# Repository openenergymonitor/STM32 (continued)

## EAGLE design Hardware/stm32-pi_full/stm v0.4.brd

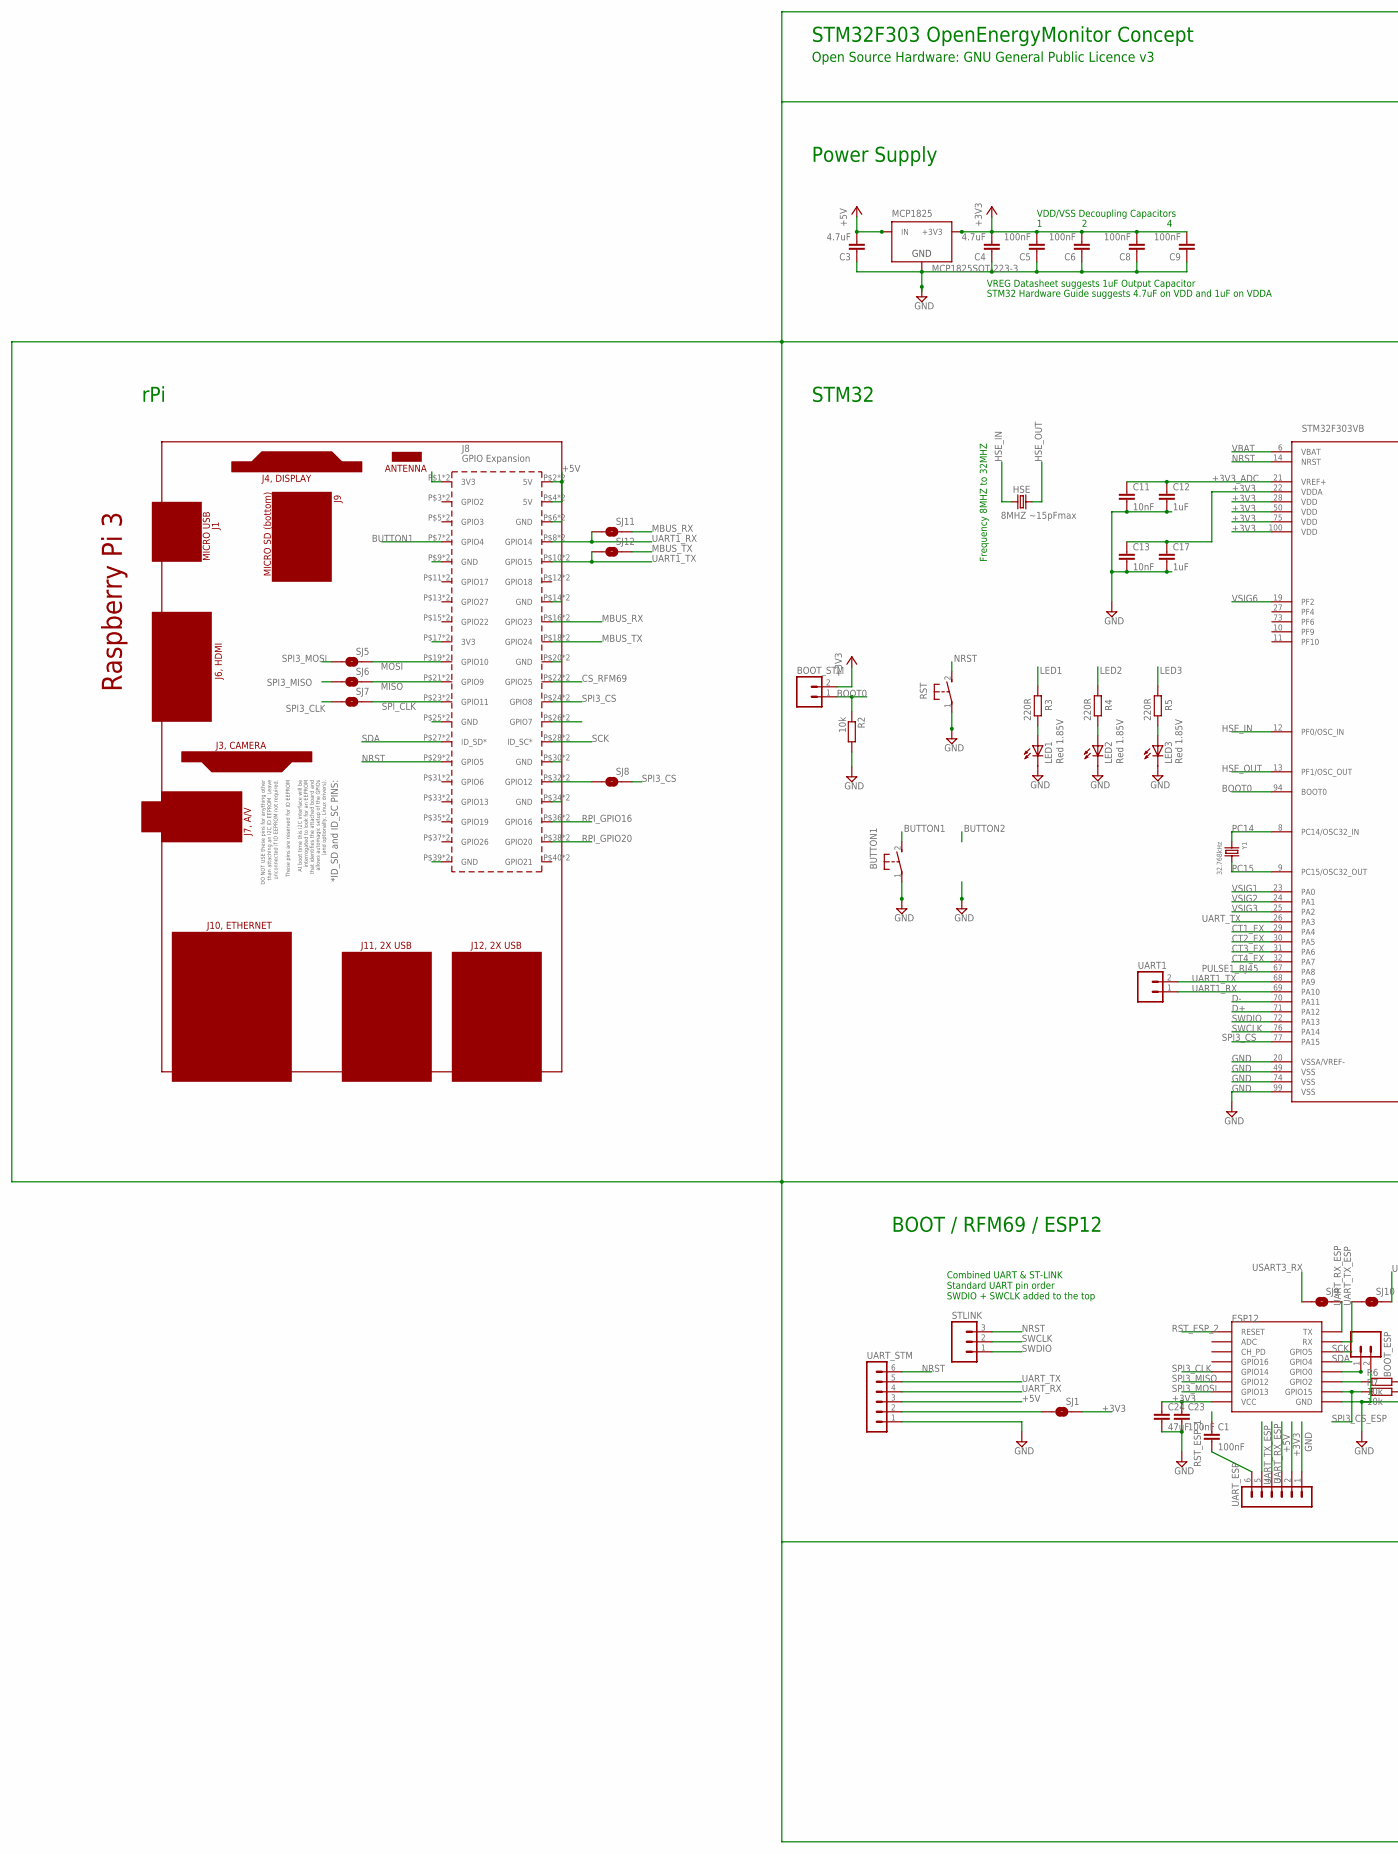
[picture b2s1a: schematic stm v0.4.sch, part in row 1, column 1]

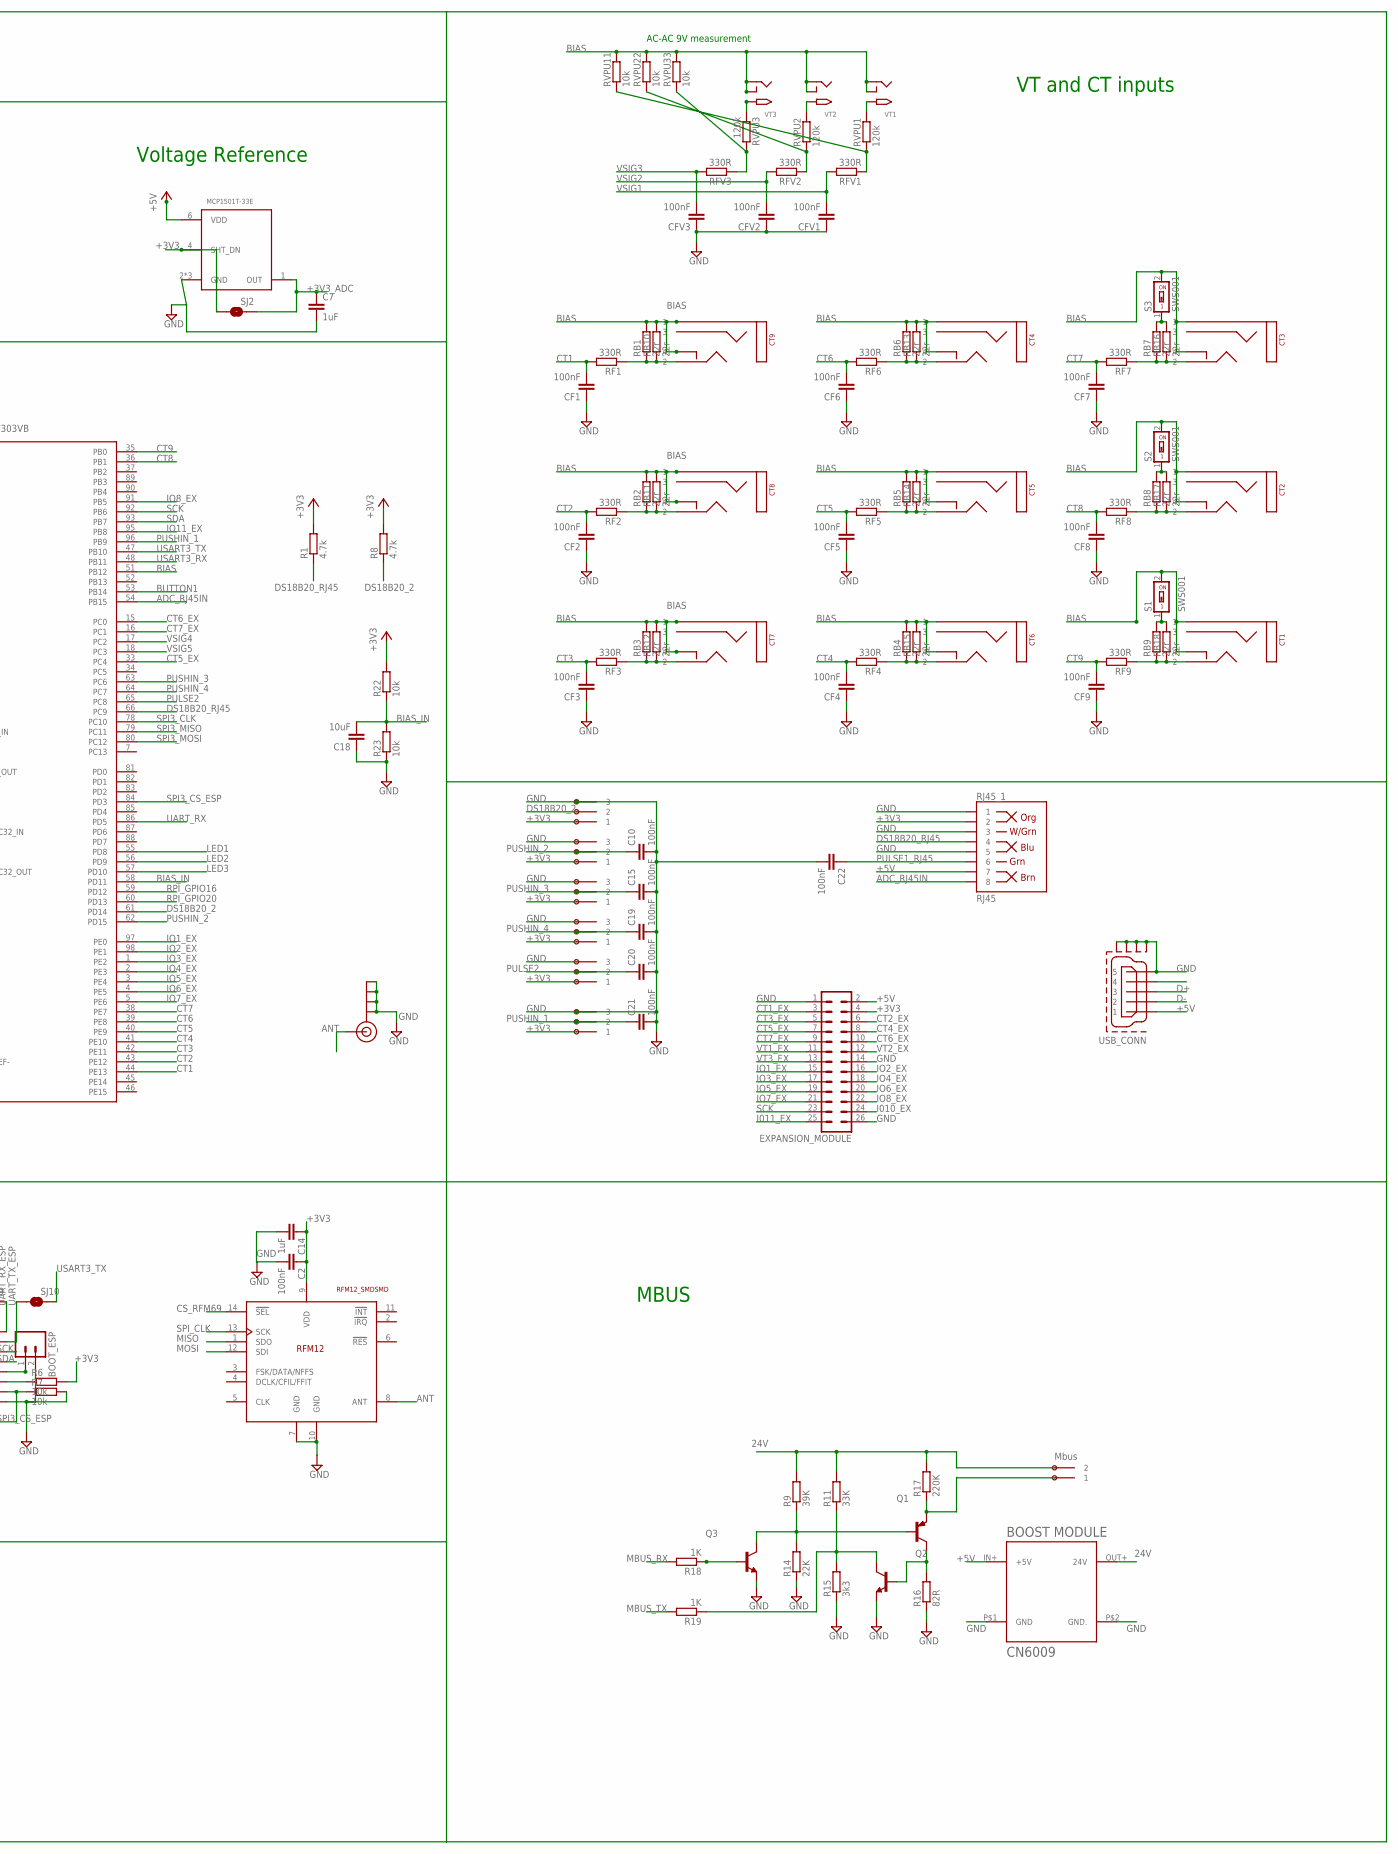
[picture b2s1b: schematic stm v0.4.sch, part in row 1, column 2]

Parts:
2POLE_MBUS: OMNIMATE_LSF_2
3POLE_1, 3POLE_2, 3POLE_3, 3POLE_4, 3POLE_5, 3POLE_6: OMNIMATE_LSF_3
BOOT_ESP: M02PTH; 1X02
BOOT_STM: M02PTH; 1X02
BUTTON1: 31-XX; B3F-31XX
C1, C2, C5, C6, C8, C9, C10, C15, C19, C20, C21, C22, C23: 100nF; C0603
C3, C4: 4.7uF; C0805
C7, C14: 1uF; C0805
C11, C13: 10nF; C0603
C12, C17: 1uF; C0603
C18: 10uF; C0603
C24: 47uF; C0805
CF1, CF2, CF3, CF4, CF5, CF6, CF7, CF8, CF9: 100nF; C0603
CFV1, CFV2, CFV3: 100nF; C0603
CT1, CT2, CT3, CT4, CT5, CT6, CT7, CT8, CT9: STEREO_SMD; STEREO_SMT
ESP12: ESP12SMD; ESP12-SMD
EXPANSION_MODULE: MA13-2
HSE: 8MHZ ~15pFmax; CTS406
J$1: SMA_EDGE; SMA-EDGE
LED1, LED2, LED3: Red 1.85V; CHIP-LED0805
MCP1825: MCP1825SOT-223-3; SOT-223
PCB2: RPI3YA; RPI3MIRROR2
Q1: MMBT3906; SOT23
Q2, Q3: MMBT3904; SOT23
R1, R8: 4.7k; R0603
R2, R6, R7, R22, R23: 10k; R0603
R3, R4, R5: 220R; R0603
R9: 39K; R0603
R11: 33K; R0603
R14: 22K; R0603
R15: 3k3; R0603
R16: 82R; R0603
R17: 220K; R0603
R18, R19: 1K; R0603
RB1, RB2, RB3, RB4, RB5, RB6, RB7, RB8, RB9: 22r; R0603
RB10, RB11, RB12, RB13, RB14, RB15, RB16, RB17, RB18: 22r; 0207/7
RF1, RF2, RF3, RF4, RF5, RF6, RF7, RF8, RF9: 330R; R0603
RFM69HCW: RFM12_SMDSMD; RFM12
RFV1, RFV2, RFV3: 330R; R0603
RJ45_1: RJ45; RJ45-8
RST: 31-XX; B3F-31XX
RVPU1, RVPU2, RVPU3: 120k; R0603
RVPU11, RVPU22, RVPU33: 10k; R0603
S1, S2, S3: SWS001; SMS-001
SJ1, SJ2, SJ5, SJ6, SJ7, SJ8, SJ9, SJ10, SJ11, SJ12: SOLDERJUMPERNO; SJ_2S-NO
STLINK: M03PTH; 1X03
STM32F303VB: STM32F303XB; TQFP100
U$2: BOOST_MODULE; BOOST
UART1: M02PTH; 1X02
UART_ESP: MA06-1
UART_STM: MA06-1
USB_CONN: MICRO-USB-RECEPTACLE47589-0001; 47589-0001
VREF_3V3: MCP1501T-33E; SOT95P280X145-6N
VT1, VT2, VT3: 2.1MMJACKSMT; DCJACK_2MM_SMT
Y1: 32.768kHz; CRYSTAL_8X3.8

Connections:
24V: 2POLE_MBUS.P$3 (2), 2POLE_MBUS.P$4 (2), R9.2, R11.2, R17.2, U$2.OUT+ (24V)
+3V3: 3POLE_1.P$1 (1), 3POLE_1.P$2 (1), 3POLE_2.P$1 (1), 3POLE_2.P$2 (1), 3POLE_3.P$1 (1), 3POLE_3.P$2 (1), 3POLE_4.P$1 (1), 3POLE_4.P$2 (1), 3POLE_5.P$1 (1), 3POLE_5.P$2 (1), 3POLE_6.P$1 (1), 3POLE_6.P$2 (1), BOOT_STM.2, C2.1, C4.2, C5.2, C6.2, C8.2, C9.2, C13.1, C14.1, C17.1, C23.1, C24.1, ESP12.VCC, EXPANSION_MODULE.4, MCP1825.3 (+3V3), R1.2, R6.2, R8.2, R22.2, RFM69HCW.9 (VDD), RJ45_1.2, SJ1.2, SJ2.1, STM32F303VB.22 (VDDA), STM32F303VB.28 (VDD), STM32F303VB.50 (VDD), STM32F303VB.75 (VDD), STM32F303VB.100 (VDD), UART_ESP.2, VREF_3V3.4 (SHT_DN)
+3V3_ADC: C7.1, C11.1, C12.1, SJ2.2, STM32F303VB.21 (VREF+), VREF_3V3.1 (OUT)
+5V: C3.2, EXPANSION_MODULE.2, MCP1825.1 (IN), PCB2.P$2 (5V), PCB2.P$4 (5V), PCB2.P$42 (5V), PCB2.P$44 (5V), RJ45_1.7, U$2.IN+ (+5V), UART_ESP.3, UART_STM.3, USB_CONN.1, VREF_3V3.6 (VDD)
AC1: RVPU1.2, VT1.PWR2 (TIP)
AC2: RVPU2.2, VT2.PWR2 (TIP)
AC3: RVPU3.1, VT3.PWR2 (TIP)
ADC0: RFV3.1, RVPU3.2, RVPU33.1
ADC_RJ45IN: RJ45_1.8, STM32F303VB.54 (PB15)
ANT: J$1.SIG (SIGNAL), RFM69HCW.8 (ANT)
BIAS: CT1.P$1 (1), CT1.P$4 (4), CT2.P$1 (1), CT2.P$4 (4), CT3.P$1 (1), CT3.P$4 (4), CT4.P$1 (1), CT4.P$4 (4), CT5.P$1 (1), CT5.P$4 (4), CT6.P$1 (1), CT6.P$4 (4), CT7.P$1 (1), CT7.P$4 (4), CT8.P$1 (1), CT8.P$4 (4), CT9.P$1 (1), CT9.P$4 (4), RB1.2, RB2.2, RB3.2, RB4.2, RB5.2, RB6.2, RB10.2, RB11.2, RB12.2, RB13.2, RB14.2, RB15.2, RVPU11.2, RVPU22.2, RVPU33.2, S1.2, S2.2, S3.2, STM32F303VB.51 (PB12), VT1.GND (RING), VT1.GNDBREAK (RING_SW), VT2.GND (RING), VT2.GNDBREAK (RING_SW), VT3.GND (RING), VT3.GNDBREAK (RING_SW)
BIAS_IN: C18.2, R22.1, R23.2, STM32F303VB.58 (PD11)
BOOT0: BOOT_STM.1, R2.1, STM32F303VB.94 (BOOT0)
BUTTON1: BUTTON1.2 (S), PCB2.P$7 (GPIO4), PCB2.P$47 (GPIO4), STM32F303VB.53 (PB14)
CS_RFM69: PCB2.P$22 (GPIO25), PCB2.P$62 (GPIO25), RFM69HCW.14 (!SEL)
CT1: CF1.2, RF1.2, STM32F303VB.44 (PE13)
CT1_EX: EXPANSION_MODULE.3, STM32F303VB.29 (PA4)
CT2: CF2.2, RF2.2, STM32F303VB.43 (PE12)
CT2_EX: EXPANSION_MODULE.6, STM32F303VB.30 (PA5)
CT3: CF3.2, RF3.2, STM32F303VB.42 (PE11)
CT3_EX: EXPANSION_MODULE.5, STM32F303VB.31 (PA6)
CT4: CF4.2, RF4.2, STM32F303VB.41 (PE10)
CT4_EX: EXPANSION_MODULE.8, STM32F303VB.32 (PA7)
CT5: CF5.2, RF5.2, STM32F303VB.40 (PE9)
CT5_EX: EXPANSION_MODULE.7, STM32F303VB.33 (PC4)
CT6: CF6.2, RF6.2, STM32F303VB.39 (PE8)
CT6_EX: EXPANSION_MODULE.10, STM32F303VB.15 (PC0)
CT7: CF7.2, RF7.2, STM32F303VB.38 (PE7)
CT7_EX: EXPANSION_MODULE.9, STM32F303VB.16 (PC1)
CT8: CF8.2, RF8.2, STM32F303VB.36 (PB1)
CT9: CF9.2, RF9.2, STM32F303VB.35 (PB0)
D+: STM32F303VB.71 (PA12), USB_CONN.3
D-: STM32F303VB.70 (PA11), USB_CONN.2
DS18B20_2: 3POLE_1.P$3 (2), 3POLE_1.P$4 (2), R8.1, STM32F303VB.61 (PD14)
DS18B20_RJ45: R1.1, RJ45_1.4, STM32F303VB.66 (PC9)
GND: 3POLE_1.P$5 (3), 3POLE_1.P$6 (3), 3POLE_2.P$5 (3), 3POLE_2.P$6 (3), 3POLE_3.P$5 (3), 3POLE_3.P$6 (3), 3POLE_4.P$5 (3), 3POLE_4.P$6 (3), 3POLE_5.P$5 (3), 3POLE_5.P$6 (3), 3POLE_6.P$5 (3), 3POLE_6.P$6 (3), BOOT_ESP.2, BUTTON1.1, C2.2, C3.1, C4.1, C5.1, C6.1, C7.2, C8.1, C9.1, C10.2, C11.2, C12.2, C13.2, C14.2, C15.2, C17.2, C18.1, C19.2, C20.2, C21.2, C22.2, C23.2, C24.2, CF1.1, CF2.1, CF3.1, CF4.1, CF5.1, CF6.1, CF7.1, CF8.1, CF9.1, CFV1.1, CFV2.1, CFV3.1, ESP12.GND, EXPANSION_MODULE.1, EXPANSION_MODULE.14, EXPANSION_MODULE.26, J$1.GND@0 (GND), J$1.GND@1 (GND), J$1.GND@2 (GND), J$1.GND@3 (GND), LED1.C, LED2.C, LED3.C, MCP1825.2 (GND), MCP1825.4 (GND), PCB2.P$6 (GND), PCB2.P$9 (GND), PCB2.P$14 (GND), PCB2.P$20 (GND), PCB2.P$25 (GND), PCB2.P$30 (GND), PCB2.P$34 (GND), PCB2.P$39 (GND), PCB2.P$46 (GND), PCB2.P$49 (GND), PCB2.P$54 (GND), PCB2.P$60 (GND), PCB2.P$65 (GND), PCB2.P$70 (GND), PCB2.P$74 (GND), PCB2.P$79 (GND), Q2.2 (E), Q3.2 (E), R2.2, R7.2, R14.1, R15.1, R16.1, R23.1, RFM69HCW.7 (GND), RFM69HCW.10 (GND), RJ45_1.1, RJ45_1.3, RJ45_1.5, RST.1, STM32F303VB.20 (VSSA/VREF-), STM32F303VB.49 (VSS), STM32F303VB.74 (VSS), STM32F303VB.99 (VSS), U$2.P$1 (GND), U$2.P$2 (GND.), UART_ESP.1, UART_STM.1, USB_CONN.5, USB_CONN.CASING1 (GND1), USB_CONN.CASING2 (GND2), USB_CONN.CASING3 (GND3), USB_CONN.CASING4 (GND4), VREF_3V3.2 (GND), VREF_3V3.3 (GND), VREF_3V3.5 (GND)
HSE_IN: HSE.1, STM32F303VB.12 (PF0/OSC_IN)
HSE_OUT: HSE.3 (2), STM32F303VB.13 (PF1/OSC_OUT)
I010_EX: EXPANSION_MODULE.24
I011_EX: EXPANSION_MODULE.25
IO1_EX: EXPANSION_MODULE.15, STM32F303VB.97 (PE0)
IO2_EX: EXPANSION_MODULE.16, STM32F303VB.98 (PE1)
IO3_EX: EXPANSION_MODULE.17, STM32F303VB.1 (PE2)
IO4_EX: EXPANSION_MODULE.18, STM32F303VB.2 (PE3)
IO5_EX: EXPANSION_MODULE.19, STM32F303VB.3 (PE4)
IO6_EX: EXPANSION_MODULE.20, STM32F303VB.4 (PE5)
IO7_EX: EXPANSION_MODULE.21, STM32F303VB.5 (PE6)
IO8_EX: EXPANSION_MODULE.22, STM32F303VB.91 (PB5)
IO11_EX: STM32F303VB.95 (PB8)
LED1: R3.2, STM32F303VB.55 (PD8)
LED2: R4.2, STM32F303VB.56 (PD9)
LED3: R5.2, STM32F303VB.57 (PD10)
MBUS_RX: PCB2.P$16 (GPIO23), PCB2.P$56 (GPIO23), R18.2, SJ11.2
MBUS_TX: PCB2.P$18 (GPIO24), PCB2.P$58 (GPIO24), R19.2, SJ12.2
MISO: PCB2.P$21 (GPIO9), PCB2.P$61 (GPIO9), RFM69HCW.1 (SDO), SJ6.2
MOSI: PCB2.P$19 (GPIO10), PCB2.P$59 (GPIO10), RFM69HCW.12 (SDI), SJ5.2
unnamed: SJ1.1, UART_STM.2
unnamed: CT9.P$2 (2), RB1.1, RB10.1, RF1.1
unnamed: LED2.A, R4.1
unnamed: LED3.A, R5.1
unnamed: BOOT_ESP.1, ESP12.GPIO0
unnamed: CT8.P$2 (2), RB2.1, RB11.1, RF2.1
unnamed: CT7.P$2 (2), RB3.1, RB12.1, RF3.1
unnamed: ESP12.GPIO2, R6.1
unnamed: PCB2.P$26 (GPIO7), PCB2.P$66 (GPIO7)
unnamed: PCB2.P$32 (GPIO12), PCB2.P$72 (GPIO12), SJ8.1
unnamed: PCB2.P$1 (3V3), PCB2.P$41 (3V3)
unnamed: PCB2.P$17 (3V3), PCB2.P$57 (3V3)
unnamed: RB9.2, RB18.2, S1.1
unnamed: RB8.2, RB17.2, S2.1
unnamed: RB7.2, RB16.2, S3.1
unnamed: 2POLE_MBUS.P$1 (1), 2POLE_MBUS.P$2 (1), Q1.2 (E), R17.1
unnamed: Q1.3 (C), Q2.1 (B), R16.2
unnamed: Q1.1 (B), Q3.3 (C), R9.1, R14.2
unnamed: Q2.3 (C), R11.1, R15.2, R19.1
unnamed: Q3.1 (B), R18.1
unnamed: RFV2.1, RVPU2.1, RVPU22.1
unnamed: RFV1.1, RVPU1.1, RVPU11.1
unnamed: CT6.P$2 (2), RB4.1, RB15.1, RF4.1
unnamed: CT5.P$2 (2), RB5.1, RB14.1, RF5.1
unnamed: CT4.P$2 (2), RB6.1, RB13.1, RF6.1
unnamed: LED1.A, R3.1
unnamed: CT3.P$2 (2), RB7.1, RB16.1, RF7.1
unnamed: CT2.P$2 (2), RB8.1, RB17.1, RF8.1
unnamed: CT1.P$2 (2), RB9.1, RB18.1, RF9.1
NRST: PCB2.P$29 (GPIO5), PCB2.P$69 (GPIO5), RST.2 (S), STLINK.3, STM32F303VB.14 (NRST), UART_STM.6
PC14: STM32F303VB.8 (PC14/OSC32_IN), Y1.P$1 (1)
PC15: STM32F303VB.9 (PC15/OSC32_OUT), Y1.P$4 (2)
PULSE1_RJ45: C22.1, RJ45_1.6, STM32F303VB.67 (PA8)
PULSE2: 3POLE_5.P$3 (2), 3POLE_5.P$4 (2), C20.1, STM32F303VB.65 (PC8)
PUSHIN_1: 3POLE_6.P$3 (2), 3POLE_6.P$4 (2), C21.1, STM32F303VB.96 (PB9)
PUSHIN_2: 3POLE_2.P$3 (2), 3POLE_2.P$4 (2), C10.1, STM32F303VB.62 (PD15)
PUSHIN_3: 3POLE_3.P$3 (2), 3POLE_3.P$4 (2), C15.1, STM32F303VB.63 (PC6)
PUSHIN_4: 3POLE_4.P$3 (2), 3POLE_4.P$4 (2), C19.1, STM32F303VB.64 (PC7)
RPI_GPIO16: PCB2.P$36 (GPIO16), PCB2.P$76 (GPIO16), STM32F303VB.59 (PD12)
RPI_GPIO20: PCB2.P$38 (GPIO20), PCB2.P$78 (GPIO20), STM32F303VB.60 (PD13)
RST_ESP_1: C1.2, UART_ESP.6
RST_ESP_2: C1.1, ESP12.RESET
SCK: ESP12.GPIO5, EXPANSION_MODULE.23, PCB2.P$28 (ID_SC*), PCB2.P$68 (ID_SC*), STM32F303VB.92 (PB6)
SDA: ESP12.GPIO4, PCB2.P$27 (ID_SD*), PCB2.P$67 (ID_SD*), STM32F303VB.93 (PB7)
SPI3_CLK: ESP12.GPIO14, SJ7.1, STM32F303VB.78 (PC10)
SPI3_CS: PCB2.P$24 (GPIO8), PCB2.P$64 (GPIO8), SJ8.2, STM32F303VB.77 (PA15)
SPI3_CS_ESP: ESP12.GPIO15, R7.1, STM32F303VB.84 (PD3)
SPI3_MISO: ESP12.GPIO12, SJ6.1, STM32F303VB.79 (PC11)
SPI3_MOSI: ESP12.GPIO13, SJ5.1, STM32F303VB.80 (PC12)
SPI_CLK: PCB2.P$23 (GPIO11), PCB2.P$63 (GPIO11), RFM69HCW.13 (SCK), SJ7.2
SWCLK: STLINK.2, STM32F303VB.76 (PA14)
SWDIO: STLINK.1, STM32F303VB.72 (PA13)
UART1_RX: PCB2.P$8 (GPIO14), PCB2.P$48 (GPIO14), SJ11.1, STM32F303VB.69 (PA10), UART1.1
UART1_TX: PCB2.P$10 (GPIO15), PCB2.P$50 (GPIO15), SJ12.1, STM32F303VB.68 (PA9), UART1.2
UART_RX: STM32F303VB.86 (PD5), UART_STM.4
UART_RX_ESP: ESP12.TXD0 (TX), SJ9.2, UART_ESP.4
UART_TX: STM32F303VB.26 (PA3), UART_STM.5
UART_TX_ESP: ESP12.RXD0 (RX), SJ10.1, UART_ESP.5
USART3_RX: SJ9.1, STM32F303VB.48 (PB11)
USART3_TX: SJ10.2, STM32F303VB.47 (PB10)
VBAT: STM32F303VB.6 (VBAT)
VSIG1: CFV1.2, RFV1.2, STM32F303VB.23 (PA0)
VSIG2: CFV2.2, RFV2.2, STM32F303VB.24 (PA1)
VSIG3: CFV3.2, RFV3.2, STM32F303VB.25 (PA2)
VSIG4: STM32F303VB.17 (PC2)
VSIG5: STM32F303VB.18 (PC3)
VSIG6: STM32F303VB.19 (PF2)
VT1_EX: EXPANSION_MODULE.11
VT2_EX: EXPANSION_MODULE.12
VT3_EX: EXPANSION_MODULE.13

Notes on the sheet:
VDD/VSS Decoupling Capacitors
VREG Datasheet suggests 1uF Output Capacitor
STM32 Hardware Guide suggests 4.7uF on VDD and 1uF on VDDA
Combined UART & ST-LINK Standard UART pin order SWDIO + SWCLK added to the top
AC-AC 9V measurement
VT and CT inputs
STM32F303 OpenEnergyMonitor Concept
Power Supply
STM32
Open Source Hardware: GNU General Public Licence v3
Frequency 8MHZ to 32MHZ
Mbus
Voltage Reference
BOOT / RFM69 / ESP12
MBUS
rPi

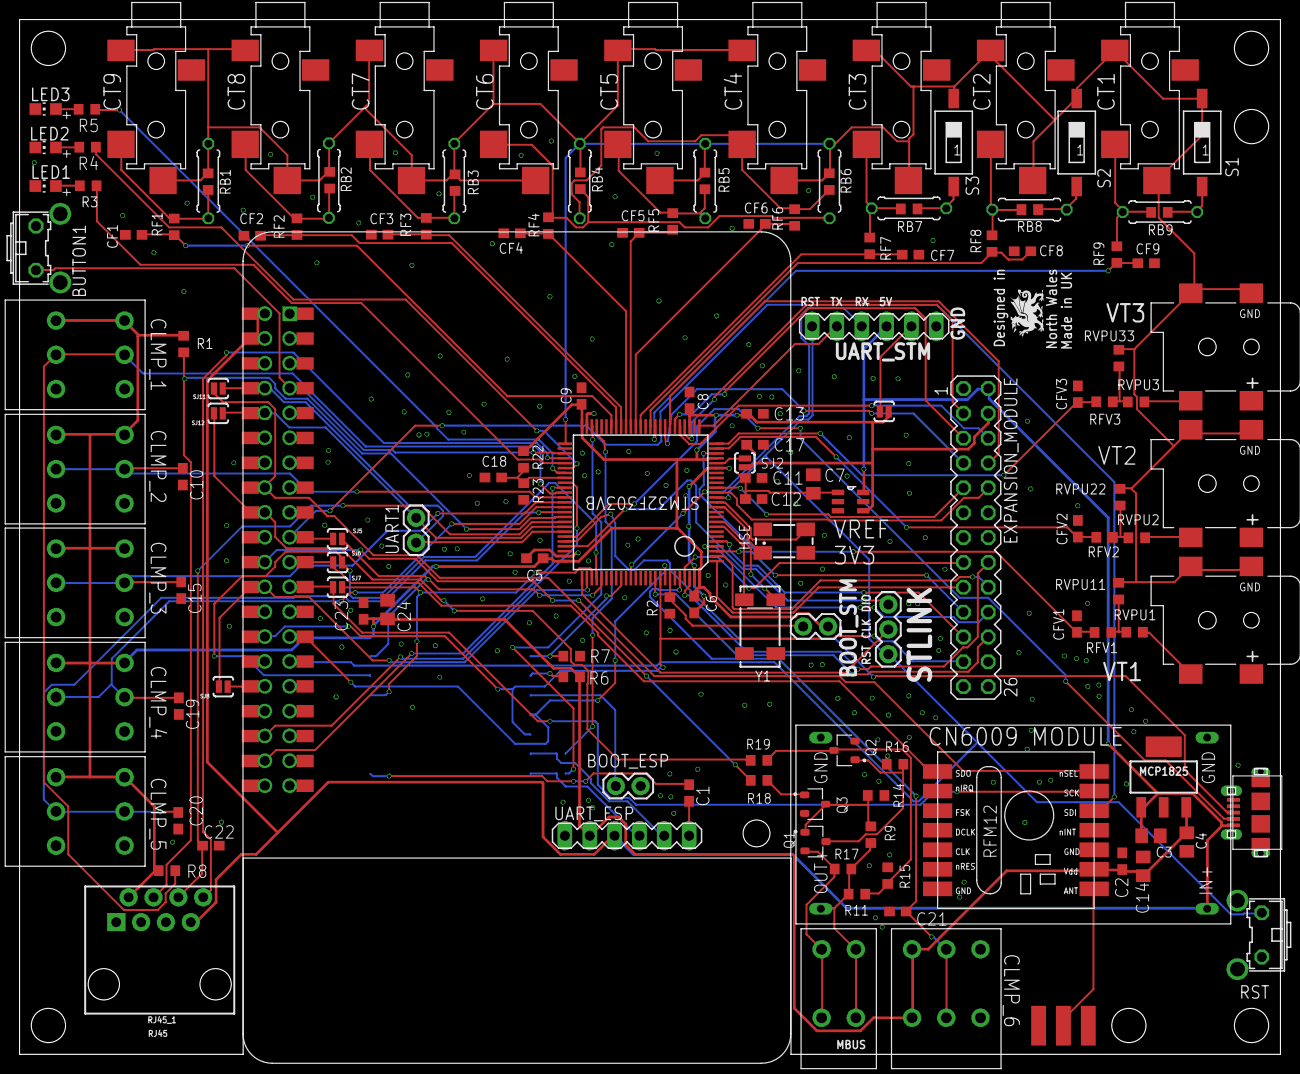
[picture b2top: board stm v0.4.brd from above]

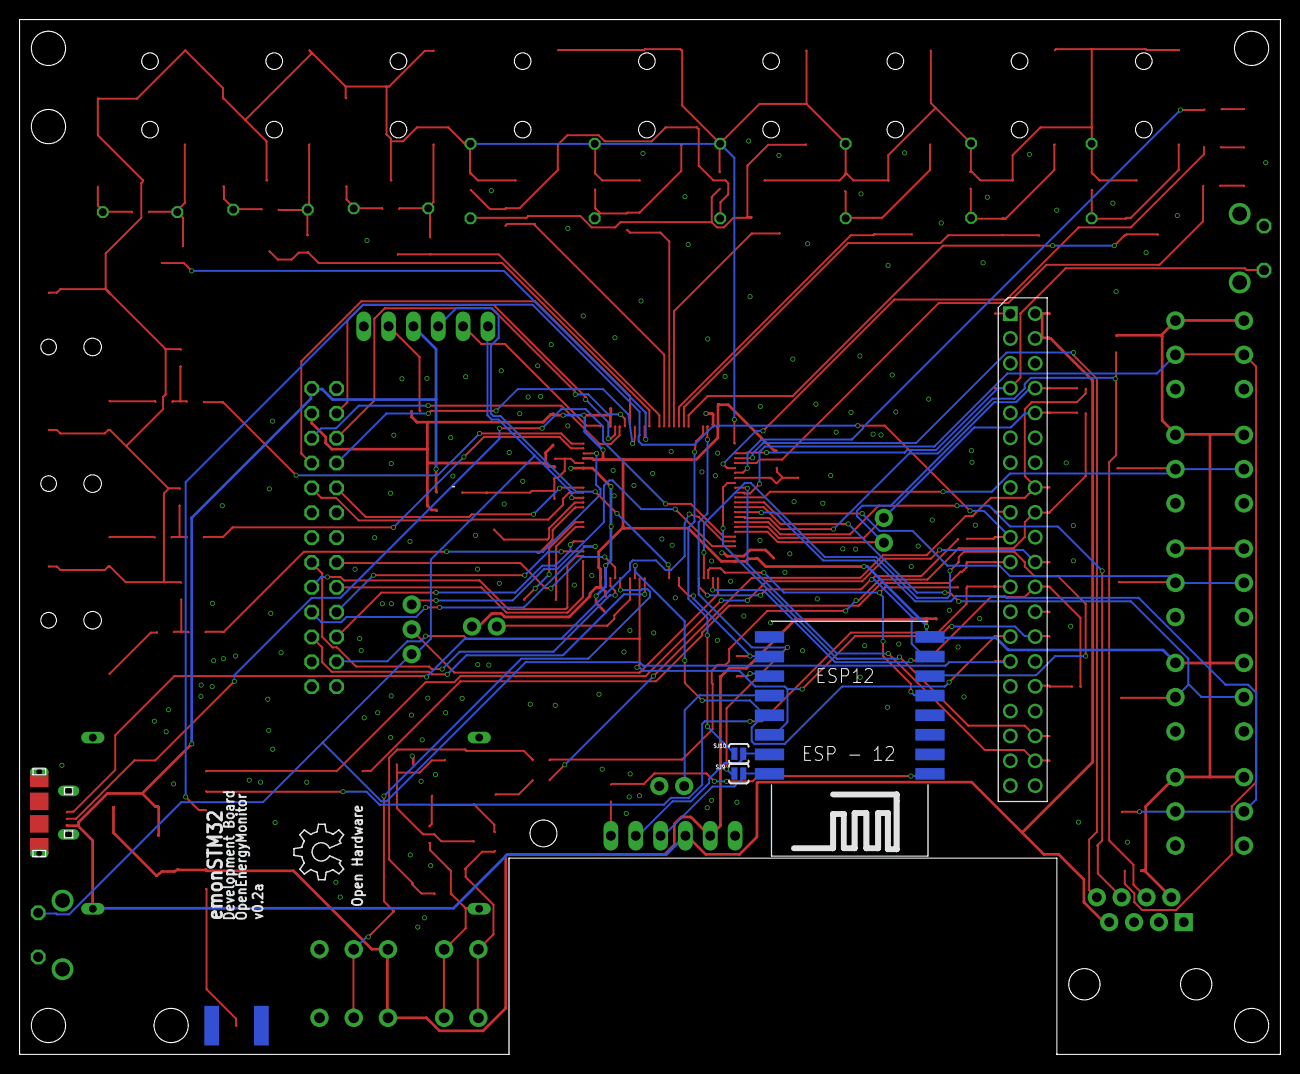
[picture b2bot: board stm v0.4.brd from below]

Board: 2 copper layers, 128.9 x 105.8 mm, 149 parts (4 on the bottom side), 116 nets.

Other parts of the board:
LOGO1: OSHW_LOGO_6MILX0200-NT; OSHW_6X200_NOTEXT

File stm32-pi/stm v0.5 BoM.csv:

Qty,Value,Device,Package,Schematic Reference,Description,CREATED_BY,DIGIKEY_PART_NUMBER,MANUFACTURER,MF,MPN,OC_FARNELL,OC_NEWARK,PACKAGE,PROD_ID,SF_ID,SPICEPREFIX,VALUE
2,,31-XX,B3F-31XX,"BUTTON1, RST",OMRON SWITCH,,,,,B3F-3100,959704,36M3582,,,,,
1,,ESP12SMD,ESP12-SMD,ESP12,ESP8266 Wifi module 12,,,,,,,,,,,,
3,,M02PTH,1X02,"BOOT_ESP, BOOT_STM, UART1",Header 2,,,,,,,,,,,,
1,,M03PTH,1X03,STLINK,Header 3,,,,,,,,,,,,
2,,MA06-1,MA06-1,"UART_ESP, UART_STM",PIN HEADER,,,,,,unknown,unknown,,,,,
1,,MA13-2,MA13-2,EXPANSION_MODULE,PIN HEADER,,,,,,unknown,unknown,,,,,
25,100nF,C-EUC0603,C0603,"C1, C2, C5, C6, C8, C9, C10, C15, C19, C20, C21, C22, C23, CF1, CF2, CF3, CF4, CF5, CF6, CF7, CF8, CF9, CFV1, CFV2, CFV3","CAPACITOR, European symbol",,,,,,,,,,,,
8,10k,R-EU_R0603,R0603,"R2, R6, R7, R22, R23, RVPU11, RVPU22, RVPU33","RESISTOR, European symbol",,,,,,,,,,,,
2,10nF,C-EUC0603,C0603,"C11, C13","CAPACITOR, European symbol",,,,,,,,,,,C,
1,10uF,C-EUC0603,C0603,C18,"CAPACITOR, European symbol",,,,,,,,,,,,
3,120k,R-EU_R0603,R0603,"RVPU1, RVPU2, RVPU3","RESISTOR, European symbol",,,,,,,,,,,,
2,1K,R-EU_R0603,R0603,"R18, R19","RESISTOR, European symbol",,,,,,,,,,,R,
2,1uF,C-EUC0603,C0603,"C12, C17","CAPACITOR, European symbol",,,,,,,,,,,,
2,1uF,C-EUC0805,C0805,"C7, C14","CAPACITOR, European symbol",,,,,,,,,,,C,
3,2.1MMJACKSMT,2.1MMJACKSMT,DCJACK_2MM_SMT,"VT1, VT2, VT3","2.1mm x 5.5mm THM DC jack with internal switch. Digikey part #PJ-102A, 4UCON part #05537",,,,,,,,,,,,
1,220K,R-EU_R0603,R0603,R17,"RESISTOR, European symbol",,,,,,,,,,,R,
3,220R,R-EU_R0603,R0603,"R3, R4, R5","RESISTOR, European symbol",,,,,,,,,,,R,
1,22K,R-EU_R0603,R0603,R14,"RESISTOR, European symbol",,,,,,,,,,,R,
9,22r,R-EU_0207/7,0207/7,"RB10, RB11, RB12, RB13, RB14, RB15, RB16, RB17, RB18","RESISTOR, European symbol",,,,,,,,,,,R,
9,22r,R-EU_R0603,R0603,"RB1, RB2, RB3, RB4, RB5, RB6, RB7, RB8, RB9","RESISTOR, European symbol",,,,,,,,,,,,
1,32.768kHz,CRYSTAL8X3.8SMT,CRYSTAL_8X3.8,Y1,Crystals,,,,,,,,,,,,
12,330R,R-EU_R0603,R0603,"RF1, RF2, RF3, RF4, RF5, RF6, RF7, RF8, RF9, RFV1, RFV2, RFV3","RESISTOR, European symbol",,,,,,,,,,,,
1,33K,R-EU_R0603,R0603,R11,"RESISTOR, European symbol",,,,,,,,,,,R,
1,39K,R-EU_R0603,R0603,R9,"RESISTOR, European symbol",,,,,,,,,,,R,
1,3k3,R-EU_R0603,R0603,R15,"RESISTOR, European symbol",,,,,,,,,,,R,
2,4.7k,R-EU_R0603,R0603,"R1, R8","RESISTOR, European symbol",,,,,,,,,,,,
2,4.7uF,C-EUC0805,C0805,"C3, C4","CAPACITOR, European symbol",,,,,,,,,,,C,
1,47uF,C-EUC0805,C0805,C24,"CAPACITOR, European symbol",,,,,,,,,,,C,
1,82R,R-EU_R0603,R0603,R16,"RESISTOR, European symbol",,,,,,,,,,,R,
1,8MHZ ~15pFmax,CRYSTALCTS406,CTS406,HSE,CRYSTAL,,,,,,unknown,unknown,,,,,
1,BOOST_MODULE,BOOST_MODULE,BOOST,U$2,,,,,,,,,,,,,
1,MCP1501T-33E,MCP1501T-33E,SOT95P280X145-6N,VREF_3V3,,,,,,,,,,,,,
1,MCP1825SOT-223-3,MCP1825SOT-223-3,SOT-223,MCP1825,MCP1825 3.3v LDO Linear Regulator,,,,,,,,,,,,
1,MICRO-USB-RECEPTACLE47589-0001,MICRO-USB-RECEPTACLE47589-0001,47589-0001,USB_CONN,MICRO USB RECEPTACLES,,,,,,,,,,,,
2,MMBT3904,MMBT3904,SOT23,"Q2, Q3",TRANS NPN 40V 0.2A SOT-23,PCB Layout,MMBT3904FSCT-ND,ON Semiconductor,,MMBT3904,,,SOT-23-3,,,,
1,MMBT3906,MMBT3906,SOT23,Q1,TRANS PNP 40V 0.2A SOT-23,PCB Layout,MMBT3906FSCT-ND,ON Semiconductor,,MMBT3906,,,SOT-23,,,,
1,OMNIMATE_LSF_2,OMNIMATE_LSF_2,OMNIMATE_LSF_2,2POLE_MBUS,,,,,,,,,,,,,
6,OMNIMATE_LSF_3,OMNIMATE_LSF_3,OMNIMATE_LSF_3,"3POLE_1, 3POLE_2, 3POLE_3, 3POLE_4, 3POLE_5, 3POLE_6",,,,,,,,,,,,,
1,RFM12_SMDSMD,RFM12_SMDSMD,RFM12,RFM69HCW,RFM12 is a low costing ISM band transceiver,,,,,,,,,,,,
1,RJ45,RJ45-8,RJ45-8,RJ45_1,RJ45 Jack - 8 pin,,,,,,,,,CONN-08506,PRT-00643,,RJ45
1,RPI3YA,RPI3YA,RPI3MIRROR2,PCB2,Device for Raspberry Pi 3 board created by Dave Young for www.element14.com,,,,,,,,,,,,
3,Red 1.85V,LEDCHIP-LED0805,CHIP-LED0805,"LED1, LED2, LED3",LED,,,,,,,,,,,,
1,SMA_EDGE,SMA_EDGE,SMA-EDGE,J$1,SMA Antenna Connector,,,,,,,,,,,,
10,SOLDERJUMPERNO,SOLDERJUMPERNO,SJ_2S-NO,"SJ1, SJ2, SJ5, SJ6, SJ7, SJ8, SJ9, SJ10, SJ11, SJ12",Solder Jumper,,,,,,,,,,,,
9,STEREO_SMD,STEREO_SMD,STEREO_SMT,"CT1, CT2, CT3, CT4, CT5, CT6, CT7, CT8, CT9",3.5mm Stereo Jack SMT,,,,,SJ-3524-SMT-TR ,,,,,,,
1,STM32F303XB,STM32F303XB,TQFP100,STM32F303VB STM32F303VD STM32F303VE (flash size),,,,,,STM32F303VBT6TR ,,,,,,,
3,SWS001,SWS001,SMS-001,"S1, S2, S3",SMD Dip Switch 1 pol.,,,,,,,,,,,,
